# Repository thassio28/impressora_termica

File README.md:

# impressora_termica
<h1>Impressora térmica  com atmega328p e cabeça térmica LTP02-245.</h1>

Para fazer uma impressão deve ser enviado o texto por meio da porta serial com o comando CR (13) "\r" ao final da frase, ao apertar o botão o texto é impresso e é retornado pela serial o texto recebido.

Tensão comunicação 3,3V
BAUD = 9600
Tensão máxima da cabeça térmica (VP) 8V.
Clock interno 8 Mhz

Código e esquema ainda em fase de desenvolvimento.

Versão 1

Video impresão de texto: https://youtube.com/shorts/1QFV2fXhjIA?feature=share

Atualização futura, impressão de imagem: https://youtube.com/shorts/7ARQ239Vu7w?feature=share

Versão 2

O controle da cabeça térmica funciona da mesma forma entre a versão 1 e 2, na versão 2 foi adicionado um conversor buck para fazer a alimentação da cabeça térmica e uma memória para guardas alguns bitmaps.

## Firmware da versão 2

Novas funções: display OLED SSD1306 128x64 (I2C) com menu, seleção de fonte, impressão de bitmap 320x240 gravado na memória SPI 25Q16 (W25Q16) e pré-visualização de texto e bitmap no display.

### Arquivos

| Arquivo | Conteúdo |
|---|---|
| `main.c` | motor de impressão, menu, protocolo serial, recepção de bitmap |
| `hw.h` | pinos da V2 (conforme `esquema_v2.pdf`) e tamanhos (bitmap, slots) |
| `spi_flash.c/.h` | SPI compartilhado e driver da memória W25Q16 |
| `oled.c/.h` | driver do SSD1306 sem framebuffer (a RAM do ATmega328 é pequena) |
| `font.h` | fontes de impressão e tabela `fontes[]` usada no menu |
| `tools/enviar.py` | envia texto, comandos e imagens pela serial (converte jpg/png para bitmap) |
| `tools/gerar_fonte.py` | gera novas fontes no formato do `font.h` |
| `teste/` | simulador no PC: roda o firmware com memória, cabeça e display simulados |

No MPLAB X, adicione `spi_flash.c` e `oled.c` ao projeto junto com o `main.c`. Também dá para compilar com `make` (avr-gcc). Ocupa cerca de 22 KB de flash e 1,4 KB de RAM.

### Uso pelo botão (com display)

- **Clique curto:** próxima opção.
- **Clique longo (> 0,7 s):** seleciona a opção.

Opções do menu:

- **Imprimir texto**
- **Fonte:** troca a fonte. A escolha fica salva na EEPROM.
- **Ver texto:** pré-visualização. Clique curto vai para a próxima tela, clique longo volta ao menu.
- **Imprimir bitmap**
- **Slot:** troca o slot da memória.
- **Ver bitmap**
- **Receber bitmap:** espera o bitmap pela serial.
- **Avançar papel**

Durante a impressão, um clique longo cancela. Sem display, o botão funciona como na V1 e imprime o texto.

### Fontes

| Nº | Nome | Tamanho | Caracteres por linha |
|---|---|---|---|
| 0 | Consolas | 16x32 | 24 |
| 1 | Terminus | 16x32 | 24 |
| 2 | Pequena (Terminus) | 8x16 | 48 |
| 3 | Grande (Consolas 2x) | 32x64 | 12 |

O texto quebra a linha entre palavras e aceita `\n`. Letras acentuadas (UTF-8) são impressas sem acento. Para adicionar uma fonte, veja o comentário no início do `font.h`.

### Bitmap

- **Formato:** 320x240 pixels, 1 bit por pixel (8 pixels por byte), linha a linha, MSB = pixel da esquerda, 1 = ponto preto, total de 9600 bytes. É o formato "horizontal" do image2cpp.
- **Slots:** 8 slots de 12 KB na memória.
- **Recepção:** os dados chegam pela UART num buffer circular de 512 bytes na RAM e são gravados na memória de 256 em 256 bytes (uma página). O tráfego da UART é controlado com XON/XOFF.
- **Impressão:** cada linha é lida da memória e enviada à cabeça centralizada (32 pontos de margem de cada lado).
- **SPI compartilhado:** a memória e a cabeça usam o mesmo SPI. Durante a impressão o SPI só é usado dentro da interrupção do Timer0, e o /CS da memória fica em nível alto quando os dados vão para a cabeça.
- **Limite de pontos:** linhas com mais de 45 pontos (limite do datasheet) são impressas em partes, com o motor parado. O valor pode ser ajustado em `MAX_PONTOS` no `main.c`.

```
pip install pyserial pillow
python3 tools/enviar.py --porta COM3 --bitmap foto.jpg --slot 0 --imprimir
python3 tools/enviar.py --porta COM3 --fonte 2 --texto "Ola mundo" --imprimir-texto
```

### Protocolo serial (9600 8N1, ESC = 0x1B)

| Comando | Função |
|---|---|
| `texto` + CR | guarda o texto (igual à V1), até 480 caracteres |
| ESC `T` | imprime o texto |
| ESC `F` n | seleciona a fonte n (`0`..`3`) |
| ESC `B` n | recebe bitmap no slot n (`0`..`7`): responde `PRONTO`, recebe 9600 bytes, responde `OK` |
| ESC `P` n | imprime o bitmap do slot n |
| ESC `V` n | mostra o bitmap do slot n no display |
| ESC `S` | responde `FONTE=f SLOT=s SLOTS=00000000` (1 = slot ocupado) |

As impressões respondem `OK`, `CANCELADO`, `ERRO sem papel` ou `ERRO temperatura`.

### Diferenças de hardware tratadas no código

- **Buck:** EN_BUCK (PD3) em nível alto desliga o conversor buck. O firmware só liga o buck durante a impressão.
- **Fim da impressão:** o DST é desconectado do timer e mantido em nível baixo, e as fases do motor são desligadas.
- **Sensor de papel:** usa borda de descida (na V1 era nível baixo, o que travava o programa sem papel).

### Simulador

`sh teste/rodar.sh` compila o `main.c` real no PC com o hardware simulado e confere os resultados:

- texto nas 4 fontes;
- recepção de bitmap com XON/XOFF;
- bitmap impresso igual ao enviado;
- limite de pontos por acionamento.

As imagens do papel e do display ficam em `teste/saida/`.

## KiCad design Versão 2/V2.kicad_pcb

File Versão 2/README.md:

<h1>Versão 2</h1>

<h2>Esquema e arquivos PCB da versão 2</h2>

<h2>Atenção: O código da versão 1 não desabilita o conversor buck</h2>

O firmware da versão 2 (main.c na raiz) controla o EN_BUCK (PD3): o buck fica desligado e só é ligado durante a impressão.

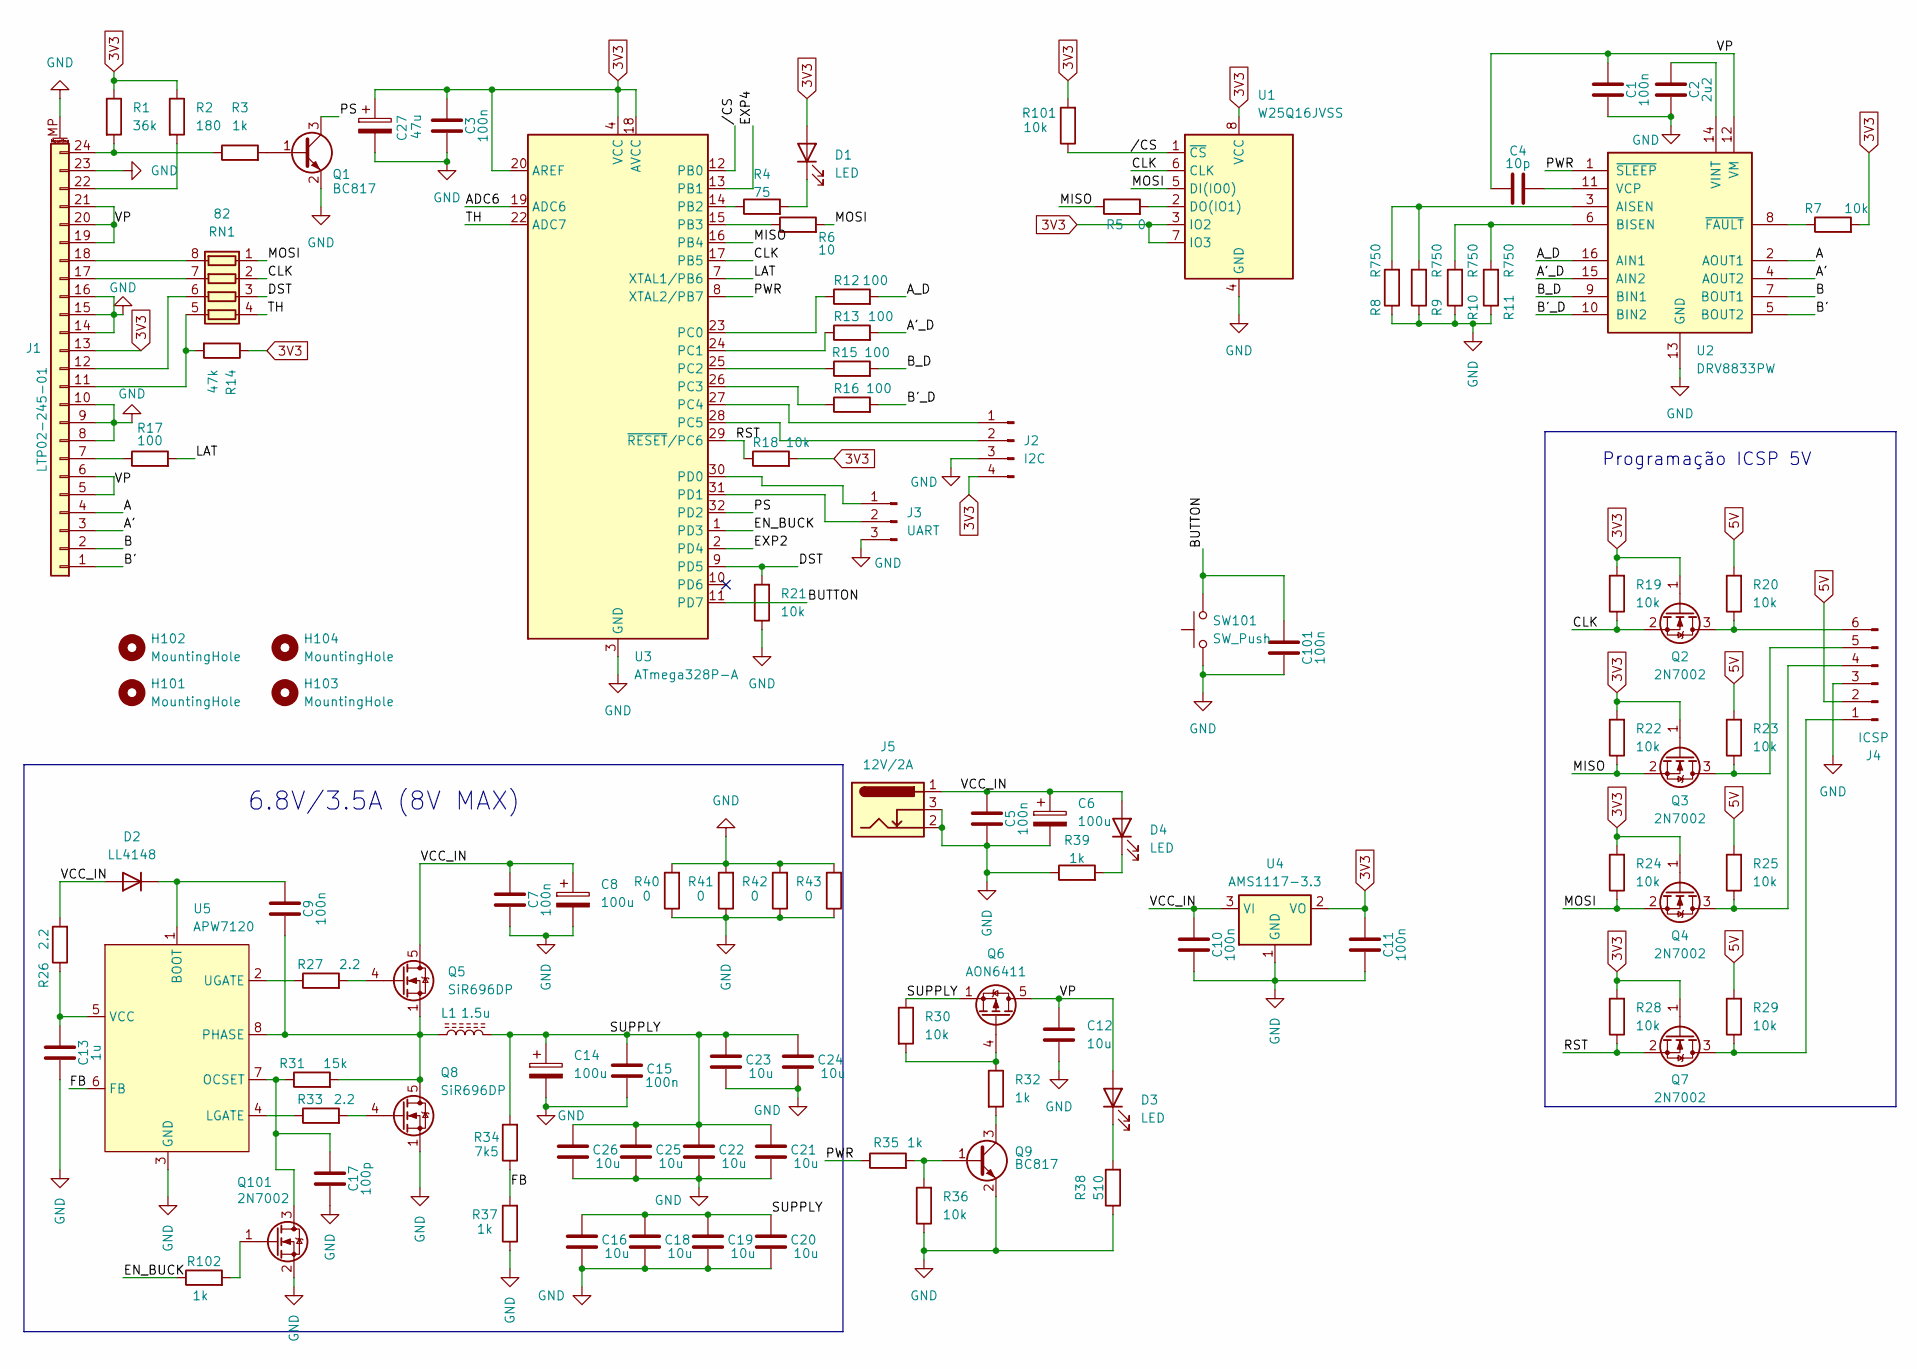
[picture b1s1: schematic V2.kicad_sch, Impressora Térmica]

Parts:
C1, C3, C5, C7, C9, C10, C11, C15, C101: 100n; C_0805_2012Metric
C2: 2u2; C_0805_2012Metric
C4: 10p; C_0805_2012Metric
C6: 100u; CP_Elec_6.3x4.5
C8, C14: 100u; CP_Elec_5x4.5
C12, C19: 10u; C_0805_2012Metric
C13: 1u; C_0805_2012Metric
C16, C18, C20, C21, C22, C23, C24, C25, C26: 10u; C_1210_3225Metric
C17: 100p; C_0603_1608Metric
C27: 47u; CP_EIA-3528-21_Kemet-B
D1, D3, D4: LED; LED_0805_2012Metric
D2: LL4148; D_MiniMELF
H101, H102, H103, H104: MountingHole; MountingHole_3.2mm_M3_DIN965
J1: LTP02-245-01; Hirose_FH12-24S-0.5SH_1x24-1MP_P0.50mm_Horizontal
J2: I2C; PinHeader_1x04_P2.54mm_Vertical
J3: UART; PinHeader_1x03_P2.54mm_Vertical
J4: ICSP; PinHeader_1x06_P2.54mm_Vertical
J5: 12V/2A; BarrelJack_GCT_DCJ200-10-A_Horizontal
L1: 1.5u; L_APV_ANR8040
Q1, Q9: BC817; SOT-23
Q2, Q3, Q4, Q7, Q101: 2N7002; SOT-23
Q5, Q8: SiR696DP; DFN8_3x3_EP_AOS
Q6: AON6411; DFN8_3x3_EP_AOS
R1: 36k; R_0603_1608Metric
R2: 180; R_0603_1608Metric
R3, R35: 1k; R_0805_2012Metric
R4: 75; R_0603_1608Metric
R5: 0; R_0603_1608Metric
R6: 10; R_0805_2012Metric
R7: 10k; R_1206_3216Metric
R8, R9, R10, R11: R750; R_0805_2012Metric
R12, R13, R15, R16: 100; R_0805_2012Metric
R14: 47k; R_0805_2012Metric
R17: 100; R_0603_1608Metric
R18: 10k; R_0805_2012Metric
R19, R20, R21, R22, R23, R24, R25, R28, R29, R30, R36, R101: 10k; R_0603_1608Metric
R26: 2.2; R_0805_2012Metric
R27, R33: 2.2; R_0603_1608Metric
R31: 15k; R_0805_2012Metric
R32, R37, R39, R102: 1k; R_0603_1608Metric
R34: 7k5; R_0603_1608Metric
R38: 510; R_0603_1608Metric
R40, R41, R42, R43: 0; R_2010_5025Metric
RN1: 82; R_Array_Convex_4x0603
SW101: SW_Push; SW_SPST_CK_RS282G05A3
U1: W25Q16JVSS; SOIC-8_5.23x5.23mm_P1.27mm
U2: DRV8833PW; TSSOP-16_4.4x5mm_P0.65mm
U3: ATmega328P-A; TQFP-32_7x7mm_P0.8mm
U4: AMS1117-3.3; SOT-223-3_TabPin2
U5: APW7120; SOIC-8_3.9x4.9mm_P1.27mm

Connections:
3V3: C3.2, C11.2, C27.1, D1.2 (A), J1.13, J2.4, Q2.1 (G), Q3.1 (G), Q4.1 (G), Q7.1 (G), R1.1, R2.1, R7.2, R14.1, R18.2, R19.2, R22.2, R24.2, R28.2, R101.2, U1.3 (IO2), U1.7 (IO3), U1.8 (VCC), U3.4 (VCC), U3.6 (VCC), U3.18 (AVCC), U3.20 (AREF), U4.2 (VO)
5V: J4.2, R20.2, R23.2, R25.2, R29.2
/A: J1.4, U2.2 (AOUT1)
/A': J1.3, U2.4 (AOUT2)
/A'_D: R13.2, U2.15 (AIN2)
/ADC6: U3.19 (ADC6)
/A_D: R12.2, U2.16 (AIN1)
/B: J1.2, U2.7 (BOUT1)
/B': J1.1, U2.5 (BOUT2)
/B'_D: R16.2, U2.10 (BIN2)
/BUTTON: C101.2, SW101.2, U3.11 (PD7)
/B_D: R15.2, U2.9 (BIN1)
/CLK: Q2.2 (S), R19.1, RN1.2 (R2.1), U1.6 (CLK), U3.17 (PB5)
/DST: R21.2, RN1.3 (R3.1), U3.9 (PD5)
/EN_BUCK: R102.1, U3.1 (PD3)
/EXP2: U3.2 (PD4)
/EXP4: U3.13 (PB1)
/FB: R34.1, R37.2, U5.6 (FB)
/LAT: R17.2, U3.7 (XTAL1/PB6)
/MISO: Q3.2 (S), R5.1, R22.1, U3.16 (PB4)
/MOSI: Q4.2 (S), R6.2, R24.1, RN1.1 (R1.1), U1.5 (DI(IO0))
/PS: Q1.3 (C), U3.32 (PD2)
/PWR: R35.1, U2.1 (~SLEEP), U3.8 (XTAL2/PB7)
/RST: Q7.2 (S), R18.1, R28.1, U3.29 (~RESET/PC6)
/SUPPLY: C14.1, C15.2, C16.2, C18.2, C19.2, C20.2, C21.2, C22.2, C23.2, C24.2, C25.2, C26.2, L1.2, Q6.1 (S), Q6.2 (S), Q6.3 (S), R30.1, R34.2
/TH: RN1.4 (R4.1), U3.22 (ADC7)
/VCC_IN: C5.2, C6.1, C7.2, C8.1, C10.2, D2.2 (A), D4.2 (A), J5.1, Q5.5 (D), R26.2, U4.3 (VI)
/VP: C1.2, C4.1, C12.1, D3.2 (A), J1.5, J1.6, J1.19, J1.20, J1.21, Q6.5 (D), U2.12 (VM)
//CS: R101.1, U1.1 (~CS), U3.12 (PB0)
GND: C1.1, C2.1, C3.1, C5.1, C6.2, C7.1, C8.2, C10.1, C11.1, C12.2, C13.1, C14.2, C15.1, C16.1, C17.1, C18.1, C19.1, C20.1, C21.1, C22.1, C23.1, C24.1, C25.1, C26.1, C27.2, C101.1, J1.8, J1.9, J1.10, J1.14, J1.15, J1.16, J1.23, J1.MP (MountPin), J2.3, J3.3, J4.3, J5.2, J5.3, Q1.2 (E), Q8.1 (S), Q8.2 (S), Q8.3 (S), Q9.2 (E), Q101.2 (S), R8.1, R9.1, R10.1, R11.1, R21.1, R36.1, R37.1, R38.1, R39.1, R40.1, R40.2, R41.1, R41.2, R42.1, R42.2, R43.1, R43.2, SW101.1, U1.4 (GND), U2.13 (GND), U3.3 (GND), U3.5 (GND), U3.21 (GND), U4.1 (GND), U5.3 (GND)
unnamed: D1.1 (K), R4.2
unnamed: C9.2, D2.1 (K), U5.1 (BOOT)
unnamed: D3.1 (K), R38.2
unnamed: D4.1 (K), R39.2
unnamed: J1.7, R17.1
unnamed: J1.11, R14.2, RN1.5 (R4.2)
unnamed: J1.12, RN1.6 (R3.2)
unnamed: J1.17, RN1.7 (R2.2)
unnamed: J1.18, RN1.8 (R1.2)
unnamed: J1.22, R2.2
unnamed: J1.24, R1.2, R3.1
unnamed: J2.1, U3.27 (PC4)
unnamed: J2.2, U3.28 (PC5)
unnamed: J3.1, U3.30 (PD0)
unnamed: J3.2, U3.31 (PD1)
unnamed: J4.1, Q7.3 (D), R29.1
unnamed: J4.4, Q4.3 (D), R25.1
unnamed: J4.5, Q3.3 (D), R23.1
unnamed: J4.6, Q2.3 (D), R20.1
unnamed: Q1.1 (B), R3.2
unnamed: Q5.4 (G), R27.2
unnamed: Q6.4 (G), R30.2, R32.1
unnamed: C9.1, L1.1, Q5.1 (S), Q5.2 (S), Q5.3 (S), Q8.5 (D), R31.2, U5.8 (PHASE)
unnamed: Q8.4 (G), R33.2
unnamed: Q9.1 (B), R35.2, R36.2
unnamed: Q9.3 (C), R32.2
unnamed: C17.2, Q101.3 (D), R31.1, U5.7 (OCSET)
unnamed: Q101.1 (G), R102.2
unnamed: R5.2, U1.2 (DO(IO1))
unnamed: R8.2, R9.2, U2.3 (AISEN)
unnamed: R10.2, R11.2, U2.6 (BISEN)
unnamed: C4.2, U2.11 (VCP)
unnamed: C2.2, U2.14 (VINT)
unnamed: R7.1, U2.8 (~FAULT)
unnamed: R4.1, U3.14 (PB2)
unnamed: R6.1, U3.15 (PB3)
unnamed: R12.1, U3.23 (PC0)
unnamed: R13.1, U3.24 (PC1)
unnamed: R15.1, U3.25 (PC2)
unnamed: R16.1, U3.26 (PC3)
unnamed: R33.1, U5.4 (LGATE)
unnamed: R27.1, U5.2 (UGATE)
unnamed: C13.2, R26.1, U5.5 (VCC)

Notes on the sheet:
6.8V/3.5A (8V MAX)
Programação ICSP 5V

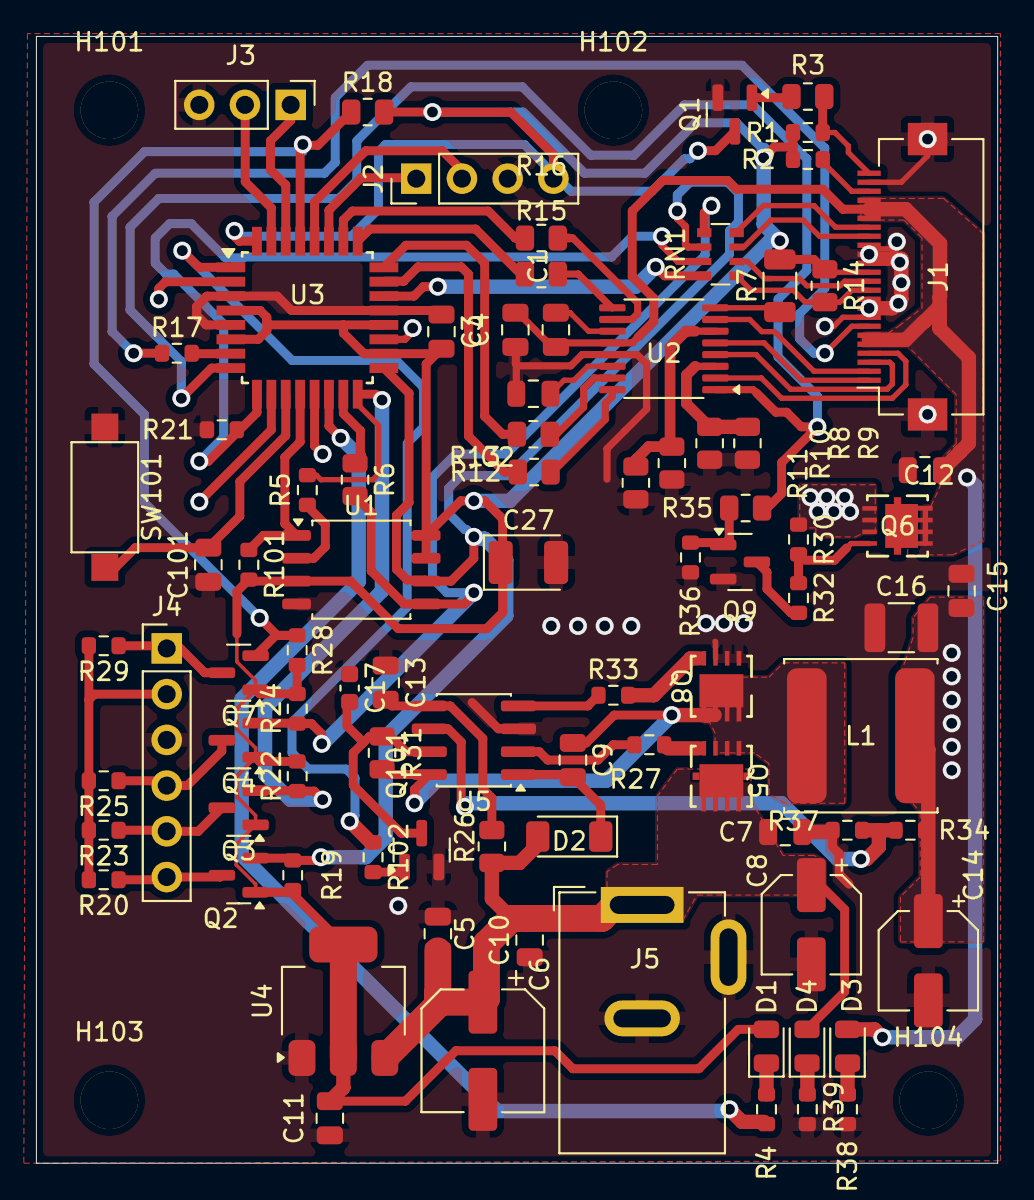
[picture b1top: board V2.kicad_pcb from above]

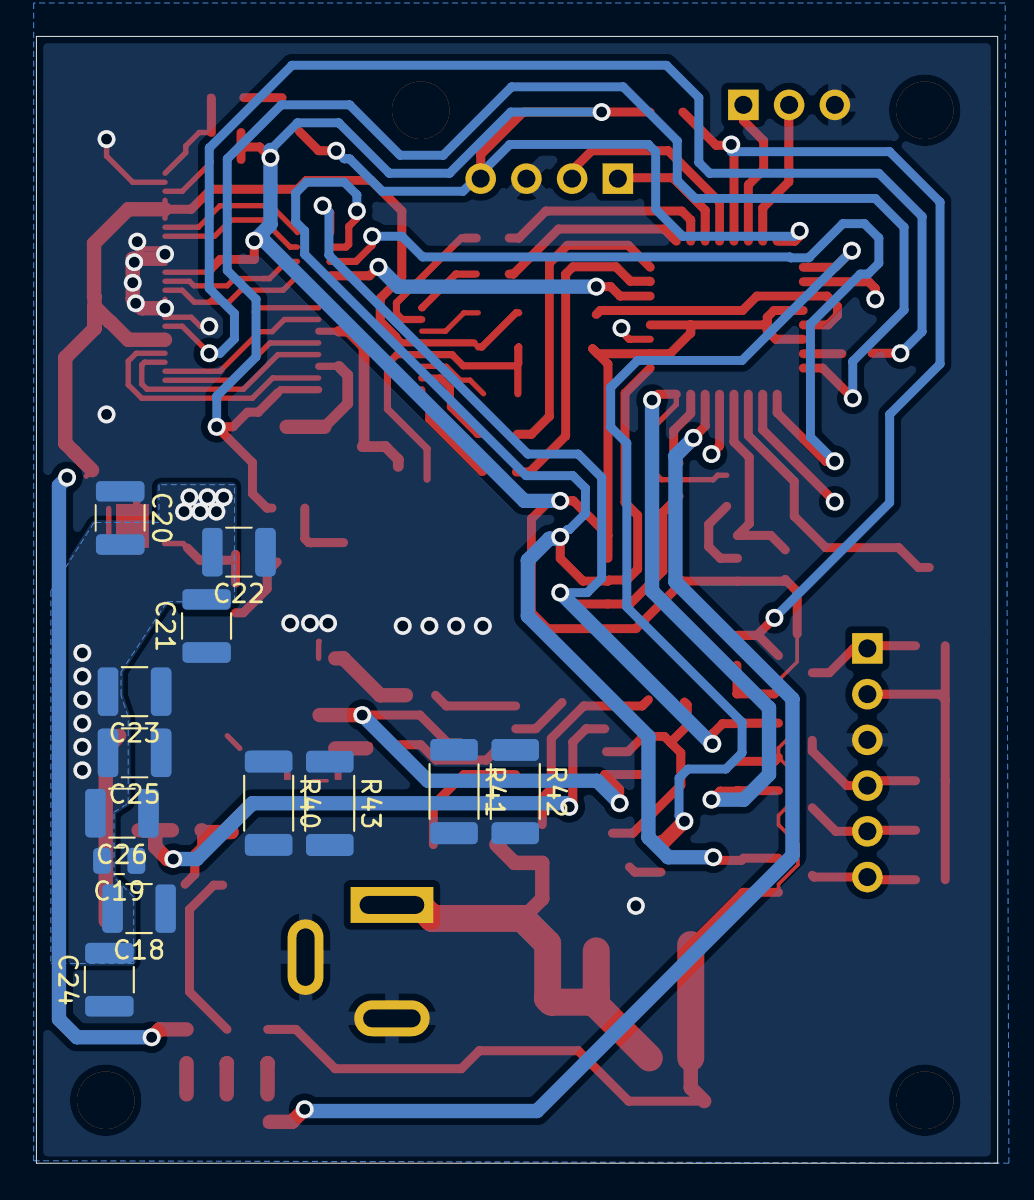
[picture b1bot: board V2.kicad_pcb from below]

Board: 2 copper layers, 53.4 x 62.6 mm, 104 parts (13 on the bottom side), 70 nets.

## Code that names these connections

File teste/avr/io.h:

/* io.h falso para o simulador no PC */
#ifndef FAKE_IO_H
#define FAKE_IO_H
#include <stdint.h>
extern volatile uint8_t DDRB, PORTB, PINB, DDRC, PORTC, DDRD, PORTD, PIND;
extern volatile uint8_t SPCR, UCSR0A, UCSR0B, UCSR0C, EICRA, EIMSK, EIFR;
extern volatile uint8_t ADMUX, ADCSRA, ADCSRB, ADCH, OCR0A, OCR0B, TCCR0A, TCCR0B;
extern volatile uint8_t TIMSK0, TCNT0, TCCR2A, TCCR2B, OCR2A, TIMSK2, SREG;
extern volatile uint16_t UBRR0;
uint16_t *sim_spdr(void);
uint8_t *sim_spsr(void);
uint16_t *sim_udr(void);
#define SPDR (*sim_spdr())
#define SPSR (*sim_spsr())
#define UDR0 (*sim_udr())
enum { PB0, PB1, PB2, PB3, PB4, PB5, PB6, PB7 };
enum { PC0, PC1, PC2, PC3, PC4, PC5, PC6 };
enum { PD0, PD1, PD2, PD3, PD4, PD5, PD6, PD7 };
#define SPE 6
#define DORD 5
#define MSTR 4
#define SPIF 7
#define SPI2X 0
#define RXCIE0 7
#define RXEN0 4
#define TXEN0 3
#define UCSZ01 2
#define UCSZ00 1
#define UDRE0 5
#define ISC01 1
#define INT0 0
#define INTF0 0
#define REFS0 6
#define ADLAR 5
#define MUX2 2
#define MUX1 1
#define MUX0 0
#define ADEN 7
#define ADSC 6
#define ADATE 5
#define ADIE 3
#define ADPS2 2
#define ADPS1 1
#define ADPS0 0
#define ADTS2 2
#define COM0B1 5
#define COM0B0 4
#define WGM01 1
#define WGM00 0
#define WGM02 3
#define CS01 1
#define CS00 0
#define TOIE0 0
#define WGM21 1
#define CS22 2
#define OCIE2A 1
#endif

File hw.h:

/*
 * File:   hw.h
 * Author: thassio lima
 *
 * Definicoes de hardware da versao 2 (ver Versão 2/esquema_v2.pdf).
 *
 *  ATmega328P - clock interno 8 MHz - 3,3 V
 *
 *  PB0  /CS  memoria W25Q16 (25Q16)
 *  PB1  EXP4 (livre)
 *  PB2  LED  (ativo em nivel baixo) - tambem e o SS do SPI, deve ser saida
 *  PB3  MOSI (memoria + cabeca termica, DI)
 *  PB4  MISO (memoria)
 *  PB5  CLK  (memoria + cabeca termica)
 *  PB6  LAT  cabeca termica (ativo em nivel baixo)
 *  PB7  PWR  liga VP (cabeca/motor) e o SLEEP do DRV8833
 *  PC0..PC3  A, A', B, B' do motor (DRV8833)
 *  PC4  SDA  display OLED SSD1306 (J2)
 *  PC5  SCL  display OLED SSD1306 (J2)
 *  PD0/PD1  UART (J3)
 *  PD2  PS   sensor de papel (INT0) - nivel baixo = sem papel
 *  PD3  EN_BUCK  nivel ALTO DESLIGA o conversor buck (Q101 puxa OCSET)
 *  PD4  EXP2 (livre)
 *  PD5  DST  strobe da cabeca termica (OC0B)
 *  PD7  BUTTON (botao para GND, usa pull-up interno)
 *  ADC7 TH   termistor da cabeca termica
 */

#ifndef HW_H
#define HW_H

#ifndef F_CPU
#define F_CPU 8000000UL
#endif

#include <avr/io.h>

#define FLASH_CS_PIN   PB0
#define LED_PIN        PB2
#define LAT_PIN        PB6
#define PWR_PIN        PB7
#define PS_PIN         PD2
#define EN_BUCK_PIN    PD3
#define DST_PIN        PD5
#define BUTTON_PIN     PD7

#define LED_ON()       (PORTB &= ~(1 << LED_PIN))
#define LED_OFF()      (PORTB |=  (1 << LED_PIN))

#ifndef FLASH_SELECT
#define FLASH_SELECT()   (PORTB &= ~(1 << FLASH_CS_PIN))
#define FLASH_DESELECT() (PORTB |=  (1 << FLASH_CS_PIN))
#endif

#define BUCK_ON()      (PORTD &= ~(1 << EN_BUCK_PIN))
#define BUCK_OFF()     (PORTD |=  (1 << EN_BUCK_PIN))

#define PWR_ON()       (PORTB |=  (1 << PWR_PIN))
#define PWR_OFF()      (PORTB &= ~(1 << PWR_PIN))

#define TEM_PAPEL()    (PIND & (1 << PS_PIN))
#define BOTAO_APERTADO() (!(PIND & (1 << BUTTON_PIN)))

/* Cabeca termica LTP02-245: 384 pontos por linha = 48 bytes */
#define CABECA_PONTOS  384
#define CABECA_BYTES   (CABECA_PONTOS / 8)

/* Bitmap: 320 x 240 pixels, 1 bit por pixel (8 pixels por byte),
 * linha a linha, MSB = pixel da esquerda, 1 = ponto preto (imprime).
 * 320 / 8 = 40 bytes por linha, 40 * 240 = 9600 bytes. */
#define BMP_LARGURA    320
#define BMP_ALTURA     240
#define BMP_BYTES_LINHA (BMP_LARGURA / 8)
#define BMP_TAMANHO    ((uint16_t)BMP_BYTES_LINHA * BMP_ALTURA)
/* margem para centralizar 320 pontos em 384: (48 - 40) / 2 = 4 bytes */
#define BMP_MARGEM     ((CABECA_BYTES - BMP_BYTES_LINHA) / 2)

/* Slots na memoria: cada slot ocupa 3 setores de 4 KB (12 KB) */
#define FLASH_SETOR       4096UL
#define SLOT_SETORES      3
#define SLOT_TAMANHO      (FLASH_SETOR * SLOT_SETORES)
#define NUM_SLOTS         8
#define SLOT_ENDERECO(s)  ((uint32_t)(s) * SLOT_TAMANHO)
/* marcador gravado logo apos os dados quando o bitmap foi recebido completo */
#define SLOT_MARCADOR_END(s) (SLOT_ENDERECO(s) + BMP_TAMANHO)
#define SLOT_MARCADOR_0   0xB1
#define SLOT_MARCADOR_1   0x7A

#endif

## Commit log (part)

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2025-02-23 Primeira versão
    Arquivo fonte e .hex, esse código permite o envio de uma frase pela porta serial e ao apertar o botão o texto é impresso.
2025-02-23 Descrição geral
2025-02-23 Esquema parcial
    Esquema não completo
2025-03-01 Versão 2
    Versão 2 do esquema com conversor buck de maior potência e conversor de nível lógico para programação ICSP.
2026-01-29 Kicad files
    Placa V2 em desenvolvimento.
